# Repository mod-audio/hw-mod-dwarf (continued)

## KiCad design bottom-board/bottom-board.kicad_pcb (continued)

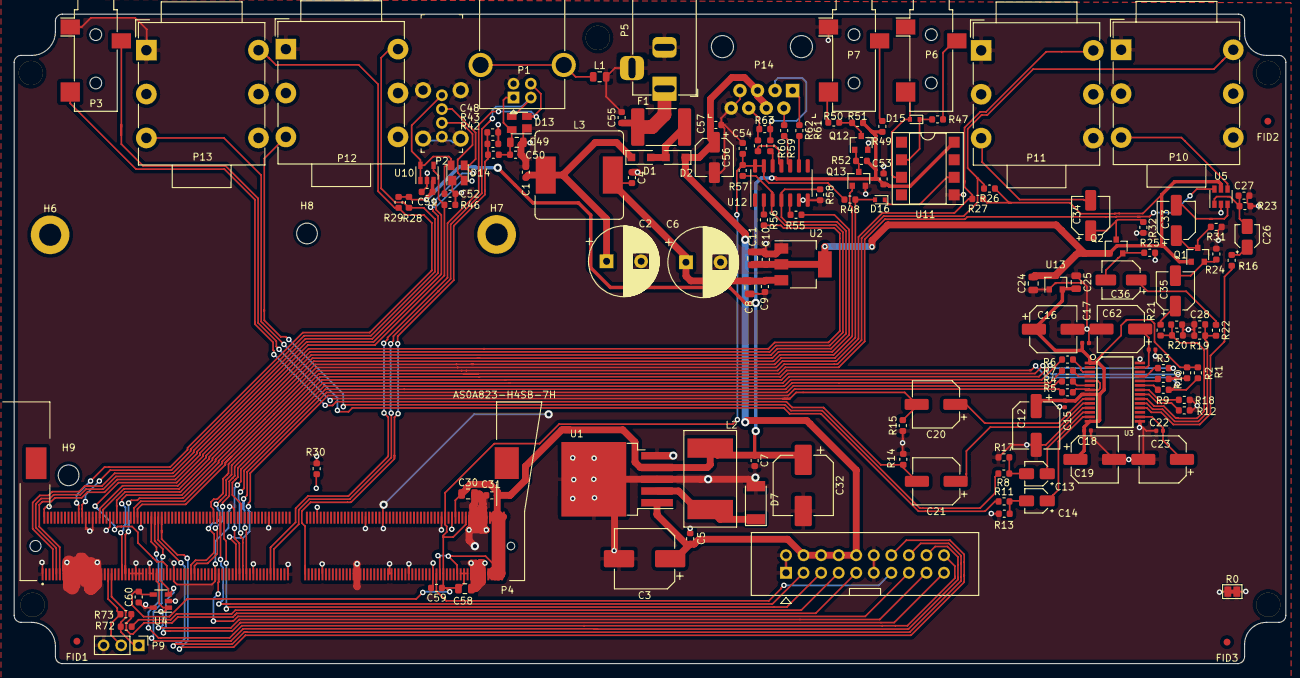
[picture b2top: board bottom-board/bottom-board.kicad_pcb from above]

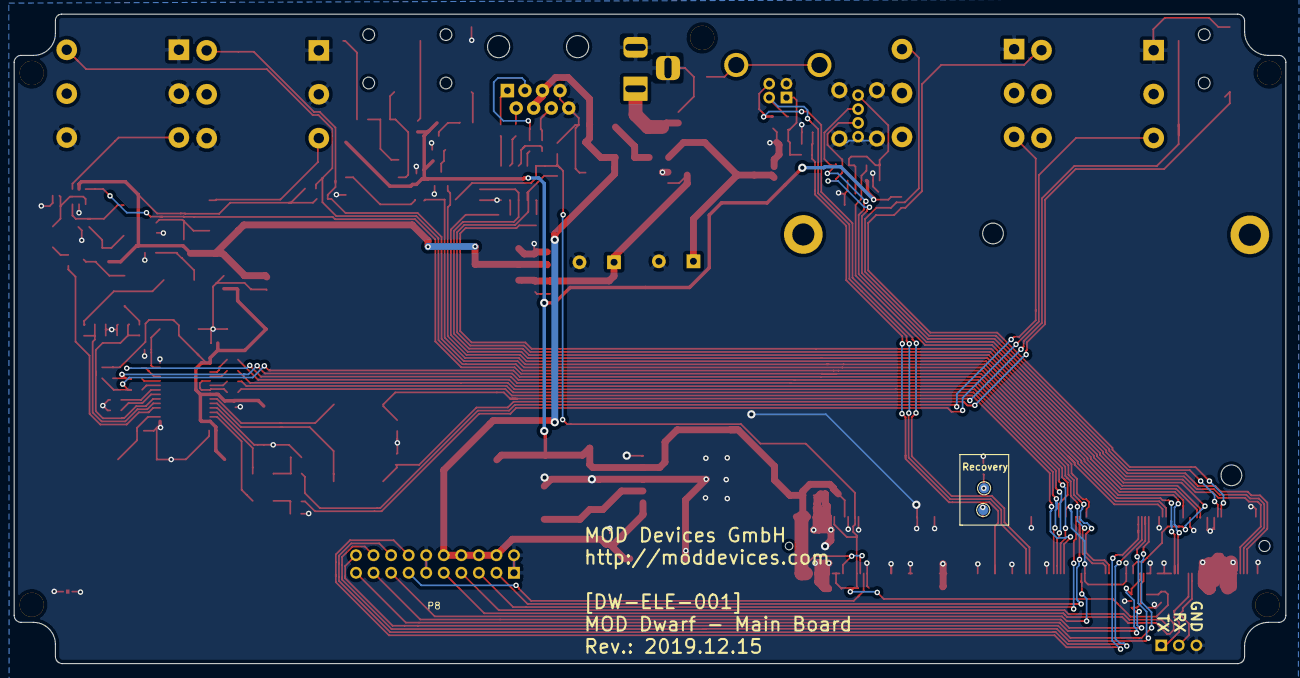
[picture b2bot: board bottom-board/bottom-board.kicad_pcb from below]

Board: 2 copper layers, 184.0 x 94.0 mm, 156 parts (2 on the bottom side), 107 nets.

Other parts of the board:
C28, C29: 220pF; C_0603_1608Metric
C55, C57: 100nF; C_0603_1608Metric
C56: 10uF; CP_Elec_5x5.3
H8, H9: HOLE; MountingHole_3mm
P3: AudioJack3; Jack_3.5mm_CUI_SJ-3523-SMT_Horizontal
P5: BARREL_JACK; BarrelJack_Horizontal
P8: HMI_DATA; Pin_Header_Straight_2x10_Shrouded
P9: SERIAL_DEBUG; PinHeader_1x03_P2.54mm_Vertical
P10, P11, P12, P13: JACK_TRS_6PINS; Jack_3.5mm_Neutrik_NMJ6HCD2_Horizontal
P14: RJ45; Ethernet_Jack_54602-908LF
R26, R27, R28, R29: 100K; R_0603_1608Metric
R72, R73: 100R; R_0603_1608Metric

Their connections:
+5V: R28.2, R29.2; also elsewhere on the board
+5VA: R26.1, R27.1; also elsewhere on the board
+12V: C56.1, C57.1, P8.4, P8.6, P8.8, P8.10, P14.4, P14.5; also elsewhere on the board
CLI_UART_RX: P9.2, R73.2; also elsewhere on the board
CLI_UART_TX: P9.1, R72.2; also elsewhere on the board
CODEC_DAC_A: P12.T; also elsewhere on the board
CODEC_DAC_B: P13.T; also elsewhere on the board
GNDA: C28.2, C29.2, C55.2, C56.2, C57.2, P3.S, P5.2, P5.3, P8.1, P8.2, P8.11, P8.12, P9.3, P10.R, P10.S, P10.TN, P11.R, P11.S, P11.TN, P12.S, P13.S, P14.7, P14.8; also elsewhere on the board
HEADPHONE_LEFT: P3.R; also elsewhere on the board
HEADPHONE_RIGHT: P3.T; also elsewhere on the board
HMI_ISP_ENABLE: P8.14; also elsewhere on the board
HMI_RESET: P8.16; also elsewhere on the board
HMI_RFU_RX: P8.5; also elsewhere on the board
HMI_RFU_TX: P8.3; also elsewhere on the board
HMI_UART_RX: P8.20; also elsewhere on the board
HMI_UART_TX: P8.18; also elsewhere on the board
IN1_DETECT: P10.SN, R26.2; also elsewhere on the board
IN2_DETECT: P11.SN, R27.2; also elsewhere on the board
LEFT_AUDIO_INPUT: P10.T; also elsewhere on the board
unnamed 48: C28.1; also elsewhere on the board
unnamed 49: C29.1; also elsewhere on the board
unnamed: P8.7, R72.1
unnamed: P8.9, R73.1
OUT1_DETECT: P12.SN, R28.1; also elsewhere on the board
OUT2_DETECT: P13.SN, R29.1; also elsewhere on the board
PM_LEDS_OE: P8.15; also elsewhere on the board
POWER_BUTTON: P8.13; also elsewhere on the board
POWER_INPUT: C55.1, P5.1; also elsewhere on the board
RIGHT_AUDIO_INPUT: P11.T; also elsewhere on the board
RS485_RX+: P14.3; also elsewhere on the board
RS485_RX-: P14.6; also elsewhere on the board
RS485_TX+: P14.1; also elsewhere on the board
RS485_TX-: P14.2; also elsewhere on the board
TWI4_SCL: P8.17; also elsewhere on the board
TWI4_SDA: P8.19; also elsewhere on the board

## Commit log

2019-12-15 add main board + documentation
2019-12-19 add fabrication files bottom board
2019-12-19 change USB host connector
2020-01-06 small changes
2020-01-06 added controller board
2020-01-08 moved USB host 1mm down
2020-01-08 reposistioned screw holes
2020-01-08 reposistioned PSU filtering caps
2020-01-09 change on MIDI input to TRS type A standart + cleanup
2020-08-05 update bottomboard
2020-10-30 rev 0.0.3
2020-11-25 change design to 4 layer PCB
2020-11-27 change posistion of connectors a tiny bit, now locked in place
2020-11-27 update BOM and schematic
2020-11-27 update manufactering data
2020-12-23 supply topboard with 5V instead of 12
2020-12-23 replace EOL usb power regulator
2020-12-23 make MIDI output type A
2020-12-23 change inp cap to 100pF instead of 100nF, also update silkscreen
2020-12-23 update production files
2020-12-23 minor cleanup
2021-09-03 cleanup BOM lines
2021-09-03 change input bias from 5 to 6 volts
2021-09-03 change recovery pads to holes, easier on production
2021-09-03 give analog bias to PX30 analog reference
2021-09-06 fix pin mapping excel
2021-09-06 change rev
2021-09-13 increase PCB size by 0.5mm, move midi connectors up by 0.5mm
2021-09-13 structure documentation folder
2021-09-14 move headphone jack up 0.5mm
2021-09-14 move mini jacks down 0.1mm
2021-09-14 swap headphone L/R
2021-09-29 add new power filter components to schematic
2021-09-29 increase som filter caps
2021-09-29 update PCB, add noisefix components
2021-09-29 clean some traces
2021-10-08 update fabrication data
2021-10-08 clean bottomboard, upload fabrication
2021-10-27 change input bias 5->6V, reduce harmonics
2021-11-10 change MPN of U10 and U12
2021-11-10 change JFET MPN
2021-11-11 correct MPN R112, U6 and U7
2021-12-20 change bottom to main-board in root folder, reversion from 1.05 to 2.0
2022-04-27 update fabrication files
2022-05-03 mainboard: add bias buffer, update MPNs, clean schematic
2022-05-04 mainboard: modify silkscreen
2022-05-04 controllerbard: change footswitches and main connector
2023-02-15 icnrease diode footprint, add extra input cap option
2023-02-15 cleanup
2023-02-22 Tweak controller board overlay
2023-02-22 updatte mainboard silkscreen
2024-10-03 README: fix link to KiCAD homepage
